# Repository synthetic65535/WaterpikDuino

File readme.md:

# WaterpikDuino
* Arduino based PCB for repair Waterpik water flosser: WP-660, WP-767, WP-672 (with two buttons and two LEDs on front panel).
* Functionality: 30+30 seconds timer, 5 minutes power-off timeout, 1/4 second massage pulses.
* IDE: KiCad
* Microcontroller fuses: Low:0xff High:0xc1 Extended:0xfd

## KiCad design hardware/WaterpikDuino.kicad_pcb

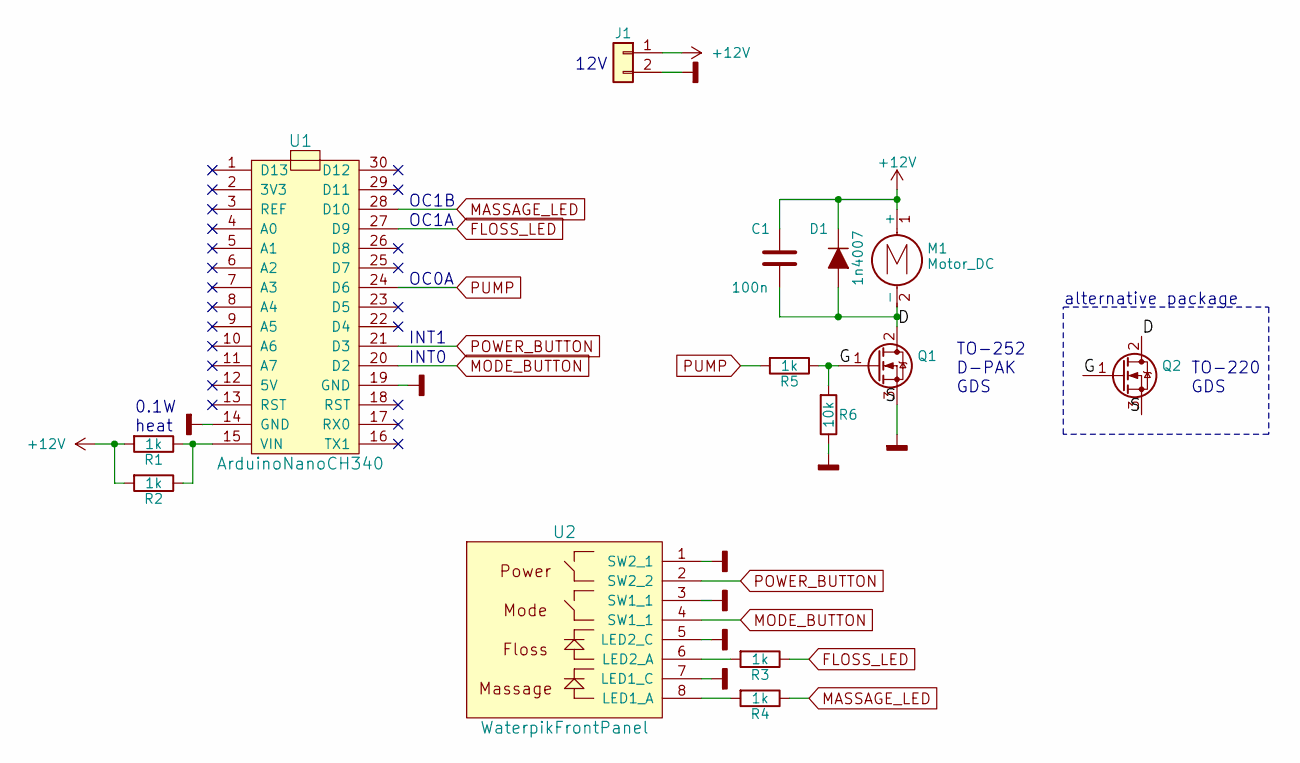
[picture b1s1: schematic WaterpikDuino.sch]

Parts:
C1: 100n; CAP
D1: 1n4007; DO-41
J1: Conn_01x02; TerminalBlock_bornier-2_P5.08mm
M1: Motor_DC; TerminalBlock_bornier-2_P5.08mm
Q1: Q_NMOS_GDS_TO252; TO-252-2
Q2: Q_NMOS_GDS_TO220; TO-220-3_Horizontal
R1, R2, R3, R4, R5: 1k; RES
R6: 10k; RES
U1: ArduinoNanoCH340
U2: WaterpikFrontPanel; Pin_Header_Straight_1x08_Pitch2.54mm

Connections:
+12V: C1.1, D1.1 (K), J1.1, M1.1 (+), R1.2, R2.2
/D: C1.2, D1.2 (A), M1.2 (-), Q1.2 (D), Q2.2 (D)
/G: Q1.1 (G), Q2.1 (G), R5.1, R6.2
FLOSS_LED: R3.1, U1.27 (D9)
GNDD: J1.2, Q1.3 (S), Q2.3 (S), R6.1, U1.14 (GND), U1.19 (GND), U2.1 (SW2_1), U2.3 (SW1_1), U2.5 (LED2_C), U2.7 (LED1_C)
MASSAGE_LED: R4.1, U1.28 (D10)
MODE_BUTTON: U1.20 (D2), U2.4 (SW1_1)
unnamed: R1.1, R2.1, U1.15 (VIN)
unnamed: R3.2, U2.6 (LED2_A)
unnamed: R4.2, U2.8 (LED1_A)
POWER_BUTTON: U1.21 (D3), U2.2 (SW2_2)
PUMP: R5.2, U1.24 (D6)

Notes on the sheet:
TO-252 D-PAK GDS
TO-220 GDS
alternative package
INT0
INT1
OC1A
OC1B
OC0A
12V
0.1W heat

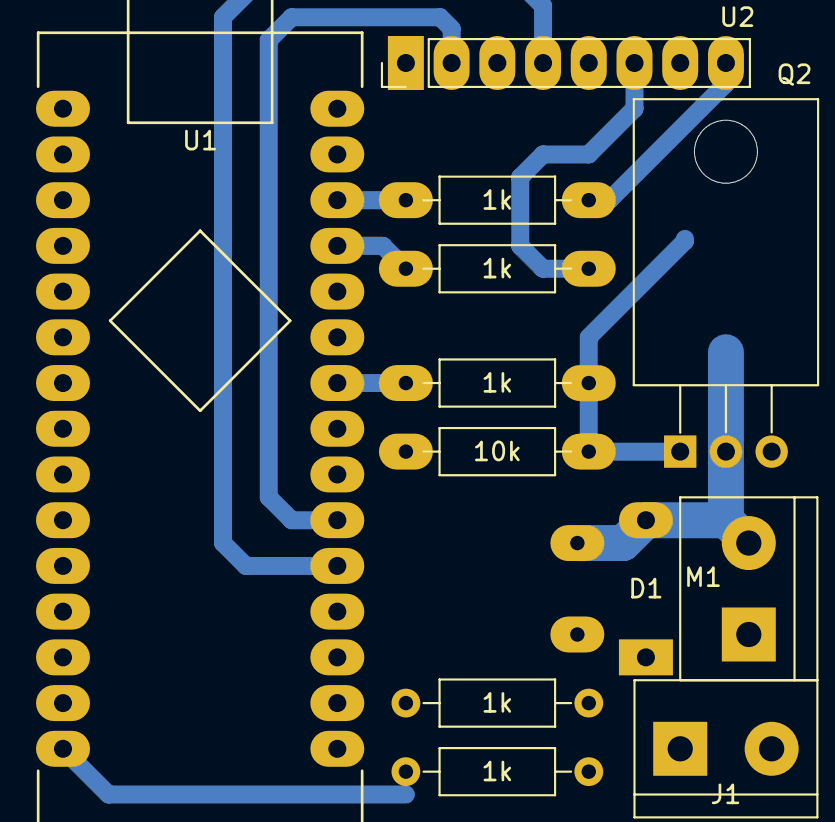
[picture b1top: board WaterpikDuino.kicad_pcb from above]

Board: 2 copper layers, 14 parts (1 on the bottom side), 12 nets.

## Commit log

2022-07-16 Readme update
